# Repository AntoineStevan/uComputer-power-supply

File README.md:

# The power supply for the µ-C1 mother board.
This repo and project contain all the files used to create the power supply for the µ-C1 mother board.

## Table Of Content.
 - [0  ](https://github.com/AntoineStevan/uComputer-power-supply/tree/main/#0-prerequisites-toc)  Prerequisites.
 - [1  ](https://github.com/AntoineStevan/uComputer-power-supply/tree/main/#1-some-images-toc)    Some images.
 - [2  ](https://github.com/AntoineStevan/uComputer-power-supply/tree/main/#2-open-in-kicad-toc)  Open in KiCAD.
 - [2.1](https://github.com/AntoineStevan/uComputer-power-supply/tree/main/#21-install-kicad-toc) Install KiCAD.
 - [2.2](https://github.com/AntoineStevan/uComputer-power-supply/tree/main/#22-use-kicad-toc)     Use KiCAD.

## 0. Prerequisites. [[toc](https://github.com/AntoineStevan/uComputer-power-supply/tree/main/#table-of-content)]
Some schematics and footprints are custom.  
One can find them [here](https://github.com/AntoineStevan/kicad-libraries).

## 1 Some images. [[toc](https://github.com/AntoineStevan/uComputer-power-supply/tree/main/#table-of-content)]
||
|:--:|
| *preview of the schematics.* |

||
|:--:|
| *preview of the pcb design (front side).* |

||
|:--:|
| *preview of the pcb design (back side).* |

## 2. Open in KiCAD. [[toc](https://github.com/AntoineStevan/uComputer-power-supply/tree/main/#table-of-content)]
This project has been designed under KiCAD, which is, according to their official website, *an open-source software tool for the creation of electronic schematic diagrams and PCB artwork.*  
All usefull official documentation can be found on the website of the Kicad software [here](https://www.kicad.org/).  
Furthermore, parts have been ordered by [Mouser](https://www.mouser.fr/) and PCBs have been manufactured by [JLCPCB](https://jlcpcb.com/).

### 2.1. Install KiCAD. [[toc](https://github.com/AntoineStevan/uComputer-power-supply/tree/main/#table-of-content)]
Official KiCAD material can be found [here](https://docs.kicad.org/5.1/en/getting_started_in_kicad/getting_started_in_kicad.html).  
Further specific material for Linux users can be found [here](https://doc.ubuntu-fr.org/kicad).

### 2.2. Use KiCAD. [[toc](https://github.com/AntoineStevan/uComputer-power-supply/tree/main/#table-of-content)]
The KiCAD team provides plenty of documentation and examples on their official website [here](https://docs.kicad.org/).  
The Internet is also full of great quality tutorials on many topics concerning KiCAD software and schematics/PCB design in general.

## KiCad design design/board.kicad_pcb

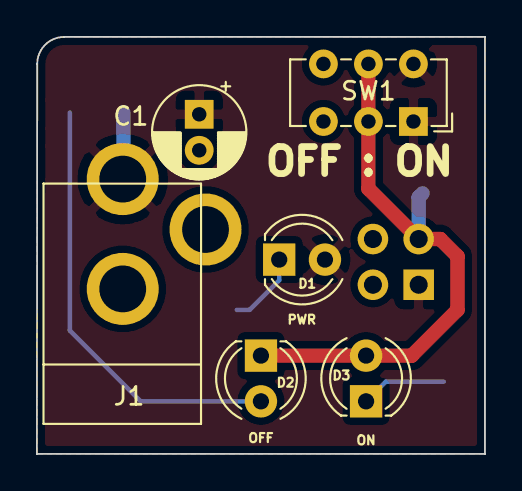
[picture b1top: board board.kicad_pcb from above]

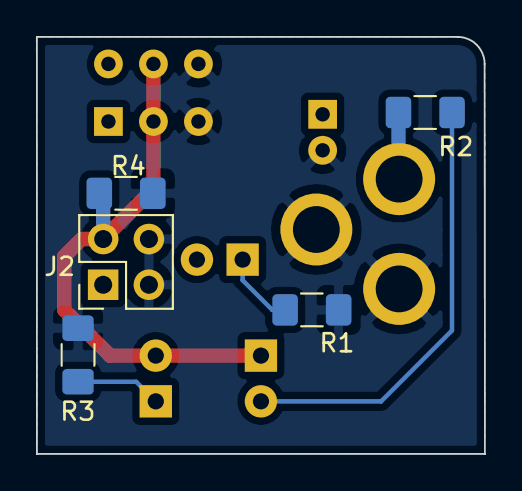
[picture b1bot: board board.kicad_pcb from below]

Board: 2 copper layers, 24.9 x 23.2 mm, 11 parts (5 on the bottom side), 6 nets.

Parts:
C1: C; CP_Radial_D5.0mm_P2.00mm
D1: PWR; LED_D4.0mm
D2: OFF; LED_D4.0mm
D3: ON; LED_D4.0mm
J1: Barrel_Jack_Switch; DC_barrel_2.1x5.5d
J2: Conn_01x04_Female; PinSocket_2x02_P2.54mm_Vertical
R1, R2, R3: 220; R_1206_3216Metric_Pad1.42x1.75mm_HandSolder
R4: 1K; R_1206_3216Metric_Pad1.42x1.75mm_HandSolder
SW1: main; SW_E-Switch_EG1271_DPDT

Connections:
/MID_OFF: D2.2, R2.2
/MID_ON: D3.1, R3.1
/MID_PWR: D1.1, R1.2
/VCC_OUT: D2.1, D3.2, J2.3, R4.2, SW1.2, SW1.5
GND: C1.2, J1.2, J1.3, J2.2, J2.4, R1.1, R3.2, R4.1, SW1.3, SW1.6
VCC: C1.1, D1.2, J1.1, J2.1, R2.1, SW1.1, SW1.4

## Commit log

2021-08-29 Draft schematics for the power supply.
2021-08-30 Swap layer for components.
2021-09-04 Start on the pcb.
2021-09-06 .gitignore.
2021-09-06 File management.
2021-09-06 New pcb design.
2021-09-06 Silk layer.
2021-09-07 Images + README update.
2021-09-07 Correct DC connector + slide switch + image update.
2021-09-07 Negative of schematics + README path correction.
2021-09-07 Correct + negative schematics.
2021-09-07 Minor changes.
2021-09-11 Link to kicad-libraries + further explainations.
